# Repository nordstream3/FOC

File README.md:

# King of FOC motor control hardware aka FOC_KING

## The DIY Open Source Vesc6 and FOC capable HW with onboard IMU and CAN
<div>

</div>

Date | Manufacturer | amount | includes | shipping & tax | price
| -------- | -------- | -------- | -------- | -------- | -------- |
2024-01-17 | JLCPCB | 10 boards | All assembled excl fets and caps | YES, to EU | $241.08

An open-source motor controller board based on a JLCPCB friendly [VESC6 75V/300A](https://vesc-project.com/sites/default/files/Benjamin%20Posts/vesc_75_300.pdf) so-called "driverless" design with individual gate drivers for all three phases. It is powered by an STM32F405 MCU and is capable of running FOC at high power and voltages.

A motor controller designed for FOC (Field Oriented Control) and HFI (High Frequency Injection), a sensorless teqnique enabling full torque at zero speed without sensor feedback. The hardware is separated in 3 sub-modules which are assembled using standard pin headers.

POWER BRIDGE | MCU | SUPPLY
|----|----|----|
 |  | 
3 phase power bridge | STM32F405 PILL | +12,+5V,+3V

Intended for "small" electric vehicles like Skateboards, OneWheels, Bicycles, Robotics, Boats, and is designed in sub-modules as a reference design for further development.

The standard design includes 12 mosfets, but it will also work with just 6 fets. You choose.

## Features
* 84V/200A continuous rating
* 20s battery voltage rating
* 3-phase FOC motor control
* 4-layer pcb design with individual gate drivers for all three phases
* STM32F405 MCU
* USB-C
* CAN, 5 mbps
* Onboard IMU (Bosch BMI270)
* Momentary on/off switch connection via 4-pin jst connector
* Led data pin for programmable LEDs
* Compact design with fets mounted on the bottom side
* 12V for gate drivers, 5V for CAN and IMU, and 3.3V for MCU and op-amped current-sense amplification
* Cheap and up-to-date with cheapest and **well stocked** components available for ordering at [JLCPCB](https://jlcpcb.com/) and [LCSC](https://www.lcsc.com)
* **Dimensions of assembled board: 65 x 78 mm**

<div>

</div>

<div>

</div>

[FOC_KING thread on esk8](https://forum.esk8.news/t/f-of-c-open-source-free-of-charge-vesc6-board-in-development-schematics-available/74888/277)

Advantages of separation into modules?
* Suitable for further development by DIY people
* Compatibility with other FOC projects
* Understanding of FOC HW is easier
* HW development is cheaper
* Debugging is easier

Disadvantages
* Assembly takes longer time. You need to solder 46 pinheader pins manually

## How to order at JLCPCB.COM

In the /production folder there is a guide for the [ordering procedure](./production/ordering_guide.md).

## How to assemble

Below is an image of the whole kit needed for assemble. The guide for the [assembly procedure](./production/README.md) is in the /production folder.

## Usage
Use the [VESC Tool](https://vesc-project.com/vesc_tool) to configure the motor controller according to your specific motor and application requirements.

## Contributions
Contributions to this project are welcome and encouraged. If you have any suggestions or improvements, please open an issue or a pull request on the GitHub repository.

## Donate
If you find this project useful and would like to support bread-and-butter for very time consuming development and maintenance, you can [donate 1$](https://www.paypal.com/donate/?business=R5QUC7RNEPKDC&no_recurring=0&item_name=A+small+but+important+contribution+for+Development+and+Maintenance.+Thank+You+very+much.&currency_code=USD) to the creator via [PayPal](https://www.paypal.com/donate/?business=R5QUC7RNEPKDC&no_recurring=0&item_name=A+small+but+important+contribution+for+Development+and+Maintenance.+Thank+You+very+much.&currency_code=USD).

## License
FOC_KING is released under the CERN Open Hardware License (OHL), developed by the European Organization for Nuclear Research. In short, it is a permissive license that allows anyone to use, modify, and distribute the licensed hardware, as long as they provide attribution to the original creators and distribute their modifications under the same license.

## Acknowledgements
FOC_KING is built on the work of the [VESC project](https://github.com/vedderb/bldc) and the contributions of its developers and contributors. Many thanks to *mxlemming* (aka [David Molony](https://github.com/davidmolony/MESC_FOC_ESC)) and *crinq* on the vesc forum on discord for their careful review and advice. Also this project is inspired by the format and concept of the [MP2](https://github.com/badgineer/MP2-ESC) by *badgineer* and the [Cheap Focer2](https://github.com/shamansystems/Cheap-FOCer-2/blob/Developer-Branch/README.md) by *shaman*.

><sub>[markdownguide.org/basic-syntax](https://www.markdownguide.org/basic-syntax/)</sub>  
><sub>[www.markdownguide.org/hacks/](https://www.markdownguide.org/hacks/)</sub>  
><sub>[support.squarespace.com Markdown-cheat-sheet](https://support.squarespace.com/hc/en-us/articles/206543587-Markdown-cheat-sheet)

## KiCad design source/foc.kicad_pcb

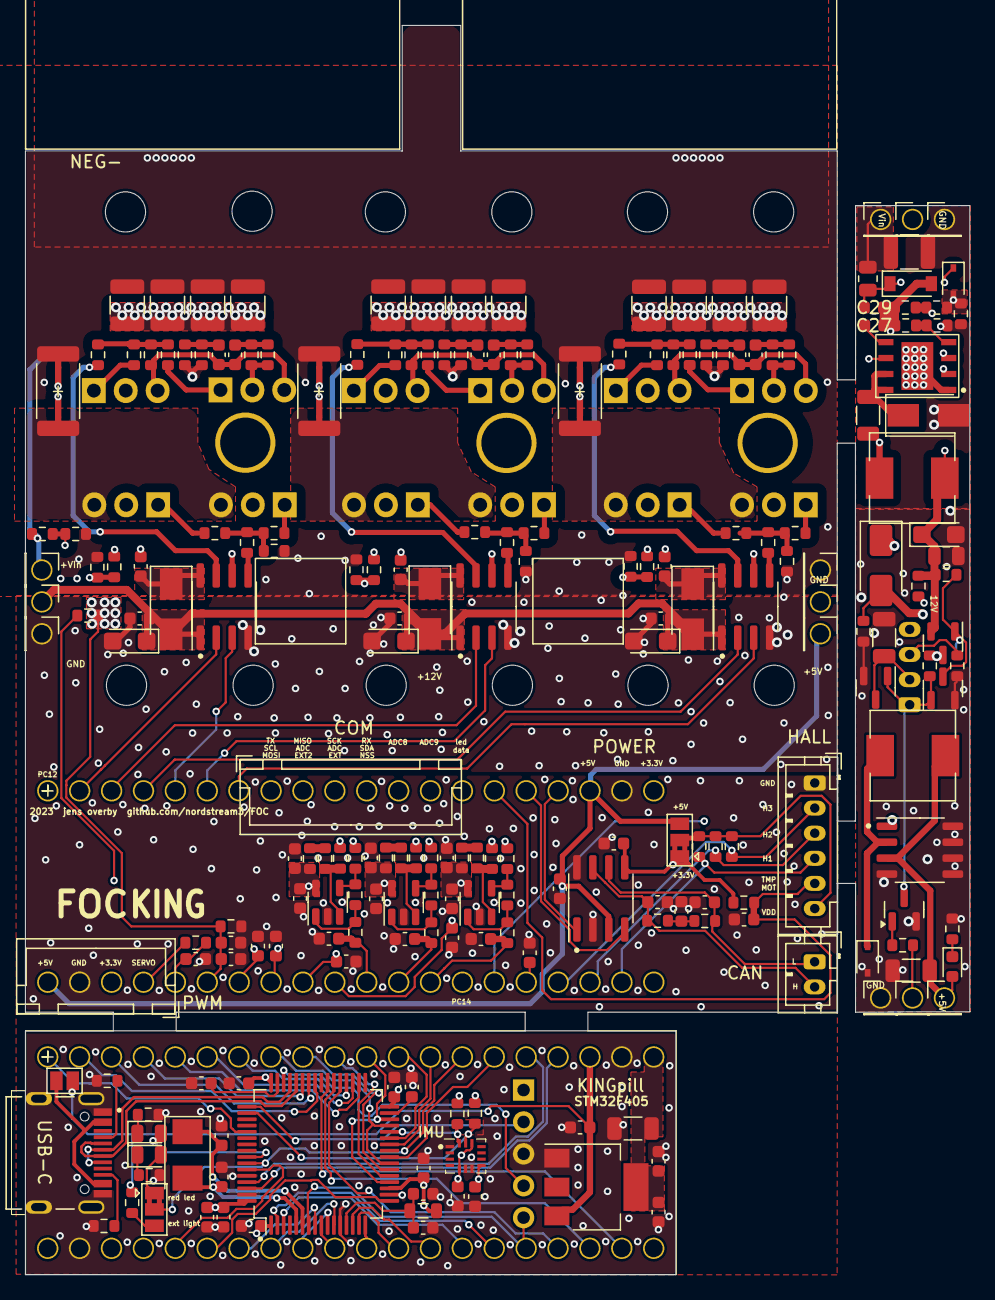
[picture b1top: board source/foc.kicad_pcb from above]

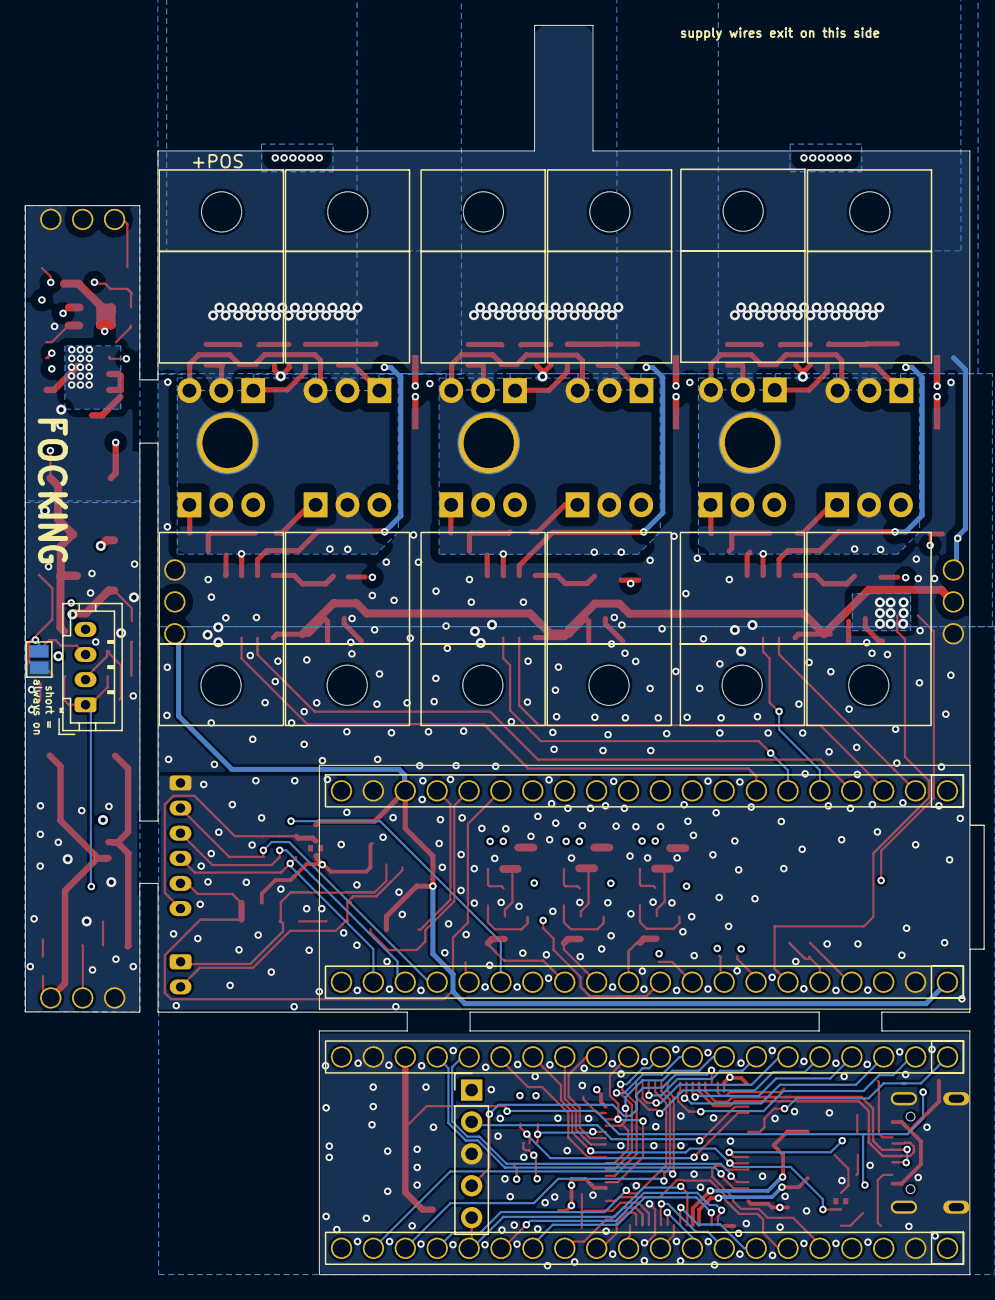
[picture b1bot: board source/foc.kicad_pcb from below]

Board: 4 copper layers, 75.2 x 99.5 mm, 259 parts (20 on the bottom side), 133 nets.

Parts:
C1, C40, C41, C50, C51, C59, C60: 4.7n; C_0603_1608Metric
C2, C3, C12, C18, C22: 100p; C_0603_1608Metric
C4, C7, C11, C15, C16, C19, C25, C27, C29, C33, C42, C45, C52, C64, C65: 2.2u; C_0603_1608Metric
C5, C6, C10, C21, C34, C43, C53, C61, C62, C63, C66, C67, C69, C72, C74: 100n; C_0603_1608Metric
C8, C13, C23: 100u@6.3V; C_1206_3216Metric
C9, C17, C24, C32: 10u; CP_EIA-3216-10_Kemet-I
C14, C20, C28, C75: 10u; C_0603_1608Metric
C26, C36, C37, C38, C39, C46, C47, C48, C49, C55, C56, C57, C58: 4.7u 100V; C_1210_3225Metric
C30, C70: 10n; C_0603_1608Metric
C31: 22u; C_0805_2012Metric
C35, C44, C54: 1n; C_0603_1608Metric
C68: 1u; C_0603_1608Metric
C71, C73: 12p; C_0603_1608Metric
CYA0650-68UH1, CYA0650-68UH2: 68uH; L_6.6x7.2_H5.0_CYA0650_68UH
D1, D2, D4, D7: US1M; D_SMA
D3: 1N5819; D_SOD-323
D5: 1N4148WS; D_SOD-323
D6: MM1W18 1W18V zener; D_SOD-123
D8: SS210; D_SMA
D9: RED; LED_0805_2012Metric
D10: GREEN; LED_0805_2012Metric
D11: WHT; LED_0603_1608Metric
H1, H2, H3, H4, H5, H6, H7, H8, H9, H10, H11, H12: MountingHole; MountingHole_3.2mm_M3
H13: Phase_A_Pad; MountingHole_3.5mm_Pad_TopOnly_custom
H14: Phase_B_Pad; MountingHole_3.5mm_Pad_TopOnly_custom
H15: Phase_C_Pad; MountingHole_3.5mm_Pad_TopOnly_custom
J1: Conn_01x02_Male; JST_PH_B2B-PH-K_1x02_P2.00mm_Vertical
J2: Conn_01x06; JST_PH_B6B-PH-K_1x06_P2.00mm_Vertical
J3: communication; JST_XH_B6B-XH-A_1x06_P2.50mm_Vertical
J4: on/off; JST_PH_B4B-PH-K_1x04_P2.00mm_Vertical
J5: servo; JST_XH_B4B-XH-A_1x04_P2.50mm_Vertical
J6: TYPE-C-31-M-12; HRO_TYPE-C-31-M-12
L1: 10n; L_0805_2012Metric
NT1, NT2, NT3, NT4, NT5, NT6: NetTie_2; NetTie-2_SMD_Pad0.5mm
P1, P2, P3, P4, P5, P6, P7, P8, P9, P10, P12, P13: SWD; PinHeader_1x01_P2.54mm_Vertical
P11: SWD; PinHeader_1x05_P2.54mm_Vertical
Q1: AO3401A; SOT-23
Q2, Q3, Q16: SS8050; SOT-23
Q4, Q5, Q6, Q7, Q8, Q9, Q10, Q11, Q12, Q13, Q14, Q15: CRST030N10N; TO-220-3_Vertical_bend
R1, R2, R3, R11, R15, R17, R19, R28: 2k; R_0603_1608Metric
R4, R5, R85: 100R; R_0603_1608Metric
R6, R13, R26, R86, R87: 5.1k; R_0603_1608Metric
R7, R10, R50, R88, R89: 10k; R_0603_1608Metric
R8, R9: 75k; R_0603_1608Metric
R12: 470k; R_0603_1608Metric
R14, R16, R18, R22, R23, R27, R38, R41, R58, R61, R76, R79: 56k @ 75V; R_0603_1608Metric
R20: 82k @ 150V; R_0805_2012Metric
R21, R24: 1k8; R_0603_1608Metric
R25: 0.1R; R_1206_3216Metric
R29, R47, R67: 150R; R_0603_1608Metric
R30, R49, R68: 30k; R_0603_1608Metric
R31, R32, R43, R44, R45, R46, R51, R52, R63, R64, R65, R66, R69, R70, R81, R82, R83, R84: 10R; R_0603_1608Metric
R33, R92, R93: 56k; R_0603_1608Metric
R34, R35, R54, R55, R72, R73, R96, R97: 1k; R_0603_1608Metric
R36, R37, R39, R40, R56, R57, R59, R60, R74, R75, R77, R78: 4.7R; R_0603_1608Metric
R42, R62, R80: 0.25mR; R_2512_6332Metric
R48: NTC 10k; R_0603_1608Metric
R53, R71, R91: 6.2k; R_0603_1608Metric
R90: 20k; R_0603_1608Metric
SW1, SW4: SW_SPDT; SolderJumper-3_P1.3mm_Bridged2Bar12_Pad1.0x1.5mm
SW2, SW3: SW_SPST; SolderJumper-2_P1.3mm_Open_Pad1.0x1.5mm
U1: TJA1051T/3/1J; SOIC-8_3.9x4.9mm_P1.27mm
U2: BMI270; Bosch_LGA-14_3x2.5mm_P0.5mm
U3: AMS1117-3.3; SOT-223-3_TabPin2
U4, U6, U7: IRS21867S; SOIC-8_3.9x4.9mm_P1.27mm
U5: XL1509-5.0E1; SOP-8_3.9x4.9mm_P1.27mm
U8: TX4130L/PW2902; TX4130L_ESOP-8
U9, U10, U11: MS8311; TSOT-23-5
U12, U13: STM32F401CCU6_Blackpill; Blackpill_STM32F401CEU6
U14: STM32F405RGT6; LQFP-64_10x10mm_P0.5mm
Y1: 8MHz Crystal Resonator, X50328MSB2GI; Crystal_SMD_5032-2Pin_5.0x3.2mm

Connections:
+5V: C4.1, C10.2, C23.1, CYA0650-68UH1.2, D11.2 (A), P4.1, P5.1, R11.1, SW1.3 (C), SW3.1 (A), U1.3 (VCC), U3.3 (VI), U5.3 (FB), U12.20 (5V), U12.38 (5V), U13.20 (5V), U13.38 (5V)
+12V: C9.1, C11.1, C17.1, C19.1, C24.1, C25.1, C31.1, C32.1, CYA0650-68UH2.2, D2.2 (A), D4.2 (A), D5.2 (A), D7.2 (A), P10.1, Q1.2 (S), R8.2, R12.2, R22.1, R26.2, U4.1 (VCC), U6.1 (VCC), U7.1 (VCC)
/driver/H1: U4.2 (HIN), U12.22 (PB13), U13.22 (PB13), U14.41 (PA8)
/driver/H2: U6.2 (HIN), U12.23 (PB14), U13.23 (PB14), U14.42 (PA9(OTG_FS_VBUS))
/driver/H3: U7.2 (HIN), U12.24 (PB15), U13.24 (PB15), U14.43 (PA10)
/driver/HO1: R31.2, U4.7 (HO)
/driver/HO2: R51.2, U6.7 (HO)
/driver/HO3: R69.2, U7.7 (HO)
/driver/HS1: C14.2, C40.1, C41.1, H13.1, Q4.3 (S), Q5.2 (D), Q6.3 (S), Q7.2 (D), R14.2, R38.1, U4.6 (VS)
/driver/HS2: C20.2, C50.1, C51.1, H14.1, Q8.3 (S), Q9.2 (D), Q10.3 (S), Q11.2 (D), R16.2, R58.1, U6.6 (VS)
/driver/HS3: C28.2, C59.1, C60.1, H15.1, Q12.3 (S), Q13.2 (D), Q14.3 (S), Q15.2 (D), R18.2, R76.1, U7.6 (VS)
/driver/L1: U4.3 (LIN), U12.25 (PA8), U13.25 (PA8), U14.34 (PB13(OTG_HS_VBUS))
/driver/L2: U6.3 (LIN), U12.26 (PA9), U13.26 (PA9), U14.35 (PB14)
/driver/L3: U7.3 (LIN), U12.27 (PA10), U13.27 (PA10), U14.36 (PB15)
/driver/LO1: R32.2, U4.5 (LO)
/driver/LO2: R52.2, U6.5 (LO)
/driver/LO3: R70.2, U7.5 (LO)
/driver/MCU_SHUTDOWN: P12.1, P13.1, R6.2, U12.6 (PA0), U13.6 (PA0), U14.2 (PC13_(RTC_AF1))
/driver/SENS_1: C12.2, R14.1, R15.1, U12.13 (PA7), U13.13 (PA7), U14.11 (PC3(ADC123_IN13))
/driver/SENS_2: C18.2, R16.1, R17.1, U12.12 (PA6), U13.12 (PA6), U14.10 (PC2(ADC123_IN12))
/driver/SENS_3: C22.2, R18.1, R19.1, U12.11 (PA5), U13.11 (PA5), U14.9 (PC1(ADC123_IN11))
/driver/SENS_SUPPLY: C30.1, R27.1, R28.1, U12.14 (PB0), U13.14 (PB0), U14.8 (PC0(ADC123_IN10))
/mcu/3.3VA: C68.1, C70.1, L1.2, U14.13 (VDDA)
/mcu/ADC_8: U12.33 (PB5), U13.33 (PB5), U14.26 (PB0(ADC12_IN8))
/mcu/ADC_9: U12.32 (PB4), U13.32 (PB4), U14.27 (PB1(ADC12_IN9))
/mcu/ADC_TEMP: C45.2, C62.1, R48.1, R50.2, U12.15 (PB1), U13.15 (PB1), U14.17 (PA3(ADC123_IN3))
/mcu/CAN_RX: U1.4 (RXD), U12.36 (PB8), U13.36 (PB8), U14.61 (PB8)
/mcu/CAN_TX: U1.1 (TXD), U12.37 (PB9), U13.37 (PB9), U14.62 (PB9)
/mcu/CURRENT_1: C35.1, R29.2, U12.10 (PA4), U13.10 (PA4), U14.16 (PA2(ADC123_IN2))
/mcu/CURRENT_2: C44.1, R47.2, U12.9 (PA3), U13.9 (PA3), U14.15 (PA1(ADC123_IN1))
/mcu/CURRENT_3: C54.1, R67.2, U12.8 (PA2), U13.8 (PA2), U14.14 (PA0(ADC123_IN0/WKUP))
/mcu/HALL_1: J2.4, R1.2, U12.2 (PC13), U13.2 (PC13), U14.39 (PC8)
/mcu/HALL_2: J2.3, R2.2, U12.3 (PC14), U13.3 (PC14), U14.38 (PC7)
/mcu/HALL_3: J2.2, R3.2, U12.4 (PC15), U13.4 (PC15), U14.37 (PC6)
/mcu/LED_GREEN: D10.2 (A), U14.57 (PB5)
/mcu/LED_RED: SW4.2 (B), U12.34 (PB6), U13.34 (PB6), U14.58 (PB6)
/mcu/MISO_ADC_EXT2: U12.29 (PA12), U13.29 (PA12), U14.22 (PA6(ADC12_IN6))
/mcu/NRST: C61.1, P11.5, U12.5 (NRST), U13.5 (NRST), U14.7 (NRST)
/mcu/PA15: R97.1, U2.13 (SCX), U14.50 (PA15(JTDI))
/mcu/PB2: R96.1, U2.14 (SDX), U14.28 (PB2-BOOT1)
/mcu/PC12: U12.21 (PB12), U13.21 (PB12), U14.53 (PC12)
/mcu/PC14: U12.7 (PA1), U13.7 (PA1), U14.3 (PC14-OSC32_IN)
/mcu/PH0: C71.1, U14.6 (PH1-OSC_OUT), Y1.1
/mcu/PH1: C73.1, U14.5 (PH0-OSC_IN), Y1.2
/mcu/RX_SDA_NSS: U12.31 (PB3), U13.31 (PB3), U14.20 (PA4(ADC12_IN4/DAC1_OUT)), U14.30 (PB11)
/mcu/SCK_ADC_EXT: U12.30 (PA15), U13.30 (PA15), U14.21 (PA5(ADC12_IN5/DAC2_OUT))
/mcu/SERVO: C63.1, R85.2, U12.16 (PB2), U13.16 (PB2), U14.59 (PB7)
/mcu/TEMP_MOTOR: C21.1, J2.5, R7.1, U12.35 (PB7), U13.35 (PB7), U14.24 (PC4(ADC12_IN14))
/mcu/TX_SCL_MOSI: U12.28 (PA11), U13.28 (PA11), U14.23 (PA7(ADC12_IN7)), U14.29 (PB10)
/mcu/USB_D+: J6.A6 (DP1), J6.B6 (DP2), U14.45 (PA12)
/mcu/USB_D-: J6.A7 (DN1), J6.B7 (DN2), U14.44 (PA11)
GND: C1.2, C2.2, C3.2, C4.2, C5.1, C6.1, C7.2, C8.2, C9.2, C10.1, C11.2, C12.1, C13.2, C15.1, C16.1, C17.2, C18.1, C19.2, C21.2, C22.1, C23.2, C24.2, C25.2, C26.1, C30.2, C31.2, C32.2, C33.2, C34.2, C35.2, C36.2, C37.2, C38.2, C39.2, C42.2, C43.2, C44.2, C45.1, C46.2, C47.2, C48.2, C49.2, C52.2, C53.2, C54.2, C55.2, C56.2, C57.2, C58.2, C61.2, C62.2, C63.2, C64.2, C65.2, C66.2, C67.2, C68.2, C69.2, C70.2, C71.2, C72.2, C73.2, C74.2, C75.2, D3.2 (A), D8.2 (A), J2.1, J6.A1B12 (GND), J6.B1A12 (GND), J6.S1 (SHIELD), J6.S2 (SHIELD), J6.S3 (SHIELD), J6.S4 (SHIELD), NT2.2, NT4.2, NT6.2, P2.1, P3.1, P8.1, P9.1, P11.3, Q2.2 (E), Q3.2 (E), Q16.2 (E), R10.2, R13.1, R15.2, R17.2, R19.2, R23.1, R26.1, R28.2, R41.1, R42.1, R44.2, R46.2, R50.1, R61.1, R62.1, R64.2, R66.2, R79.1, R80.1, R82.2, R84.2, R86.2, R87.2, R88.1, R89.1, R90.1, SW2.2 (B), U1.2 (GND), U1.8 (S), U2.1 (SDO), U2.6 (GNDIO), U2.7 (GND), U3.1 (GND), U4.4 (COM), U5.4 (O/O), U5.5 (GND), U5.6 (GND), U5.7 (GND), U5.8 (GND), U6.4 (COM), U7.4 (COM), U9.2 (V-), U10.2 (V-), U11.2 (V-), U12.19 (GND), U12.39 (GND), U13.19 (GND), U13.39 (GND), U14.12 (VSSA), U14.18 (VSS), U14.60 (BOOT0(VPP)), U14.63 (VSS)
unnamed: C1.1, R4.1, R5.2
unnamed: C40.2, R43.1, R45.1
unnamed: C41.2, R44.1, R46.1
unnamed: C50.2, R63.1, R65.1
unnamed: C51.2, R64.1, R66.1
unnamed: C59.2, R81.1, R83.1
unnamed: C60.2, R82.1, R84.1
unnamed: D1.2 (A), Q1.3 (D), R9.2, R13.2
unnamed: D1.1 (K), J4.4, P1.1, U5.1 (Vin)
unnamed: C14.1, D2.1 (K), U4.8 (VB)
unnamed: CYA0650-68UH1.1, D3.1 (K), U5.2 (Vout)
unnamed: C20.1, D4.1 (K), U6.8 (VB)
unnamed: C27.2, D5.1 (K), D6.1 (K), R20.1, U8.2 (VDD)
unnamed: C27.1, C29.2, CYA0650-68UH2.1, D6.2 (A), R21.1, R24.1, R25.1, U8.6 (VSS)
unnamed: C28.1, D7.1 (K), U7.8 (VB)
unnamed: D8.1 (K), R25.2, U8.7 (VSEN), U8.8 (VSEND)
unnamed: D9.2 (A), SW4.1 (A)
unnamed: D9.1 (K), R88.2
unnamed: D10.1 (K), R89.2
unnamed: D11.1 (K), R90.2
unnamed: C3.1, J1.1, R5.1, U1.6 (CANL)
unnamed: C2.1, J1.2, R4.2, U1.7 (CANH)
unnamed: J2.6, R1.1, R2.1, R3.1, SW1.2 (B)
unnamed: J4.1, Q2.1 (B), Q3.1 (B), Q16.3 (C), R9.1
unnamed: C8.1, J4.2, Q3.3 (C), R12.1
unnamed: J4.3, R10.1
unnamed: R85.1, U12.17 (PB10)
unnamed: J6.A5 (CC1), R86.1
unnamed: J6.B5 (CC2), R87.1
unnamed: NT1.1, R34.1
unnamed: NT2.1, R35.1
unnamed: NT3.1, R54.1
unnamed: NT4.1, R55.1
unnamed: NT5.1, R72.1
unnamed: NT6.1, R73.1
unnamed: P11.2, U14.49 (PA14(JTCK-SWCLK))
unnamed: P11.4, U14.46 (PA13(JTMS-SWDIO))
unnamed: Q1.1 (G), Q2.3 (C), R8.1, SW2.1 (A)
unnamed: Q4.1 (G), R36.1
unnamed: Q5.1 (G), R39.1
unnamed: NT1.2, Q5.3 (S), Q7.3 (S), R42.2
unnamed: Q6.1 (G), R37.1
unnamed: Q7.1 (G), R40.1
unnamed: Q8.1 (G), R56.1
unnamed: Q9.1 (G), R59.1
unnamed: Q10.1 (G), R57.1
unnamed: Q11.1 (G), R60.1
unnamed: NT3.2, Q9.3 (S), Q11.3 (S), R62.2
unnamed: Q12.1 (G), R74.1
unnamed: Q13.1 (G), R77.1
unnamed: NT5.2, Q13.3 (S), Q15.3 (S), R80.2
unnamed: Q14.1 (G), R75.1
unnamed: Q15.1 (G), R78.1
unnamed: Q16.1 (B), R6.1
unnamed: R29.1, R30.2, U9.1
unnamed: R31.1, R36.2, R37.2, R38.2
unnamed: R32.1, R39.2, R40.2, R41.2
unnamed: R33.2, R91.1
unnamed: R47.1, R49.2, U10.1
unnamed: R51.1, R56.2, R57.2, R58.2
unnamed: R52.1, R59.2, R60.2, R61.2
unnamed: R53.1, R92.2
unnamed: R67.1, R68.2, U11.1
unnamed: R69.1, R74.2, R75.2, R76.2
unnamed: R70.1, R77.2, R78.2, R79.2
unnamed: R71.1, R93.2
unnamed: J6.A4B9 (VBUS), J6.B4A9 (VBUS), SW3.2 (B)
unnamed: R11.2, SW4.3 (C)
unnamed: R21.2, R22.2, U8.3 (FB1)
unnamed: R23.2, R24.2, U8.4 (FB2)
unnamed: C29.1, U8.5 (LDO)
unnamed: R33.1, R35.2, U9.3 (+)
unnamed: R30.1, R34.2, U9.4 (-)
unnamed: R55.2, R92.1, U10.3 (+)
unnamed: R49.1, R54.2, U10.4 (-)
unnamed: R73.2, R93.1, U11.3 (+)
unnamed: R68.1, R72.2, U11.4 (-)
unnamed: C65.1, U14.31 (VCAP1)
unnamed: C64.1, U14.47 (VCAP2)
VCC: C5.2, C6.2, C7.1, C13.1, C15.2, C16.2, C33.1, C34.1, C42.1, C43.1, C52.1, C53.1, C66.1, C67.1, C69.1, C72.1, C74.1, C75.1, L1.1, P11.1, R7.2, R48.2, R53.2, R71.2, R91.2, R96.2, R97.2, SW1.1 (A), U1.5 (VIO), U2.5 (VDDIO), U2.8 (VDD), U2.12 (CSB), U3.2 (VO), U9.5 (V+), U10.5 (V+), U11.5 (V+), U12.18 (3V3), U12.40 (3V3), U13.18 (3V3), U13.40 (3V3), U14.1 (VBAT), U14.19 (VDD), U14.32 (VDD), U14.48 (VDD), U14.64 (VDD)
V_IN: C26.2, C36.1, C37.1, C38.1, C39.1, C46.1, C47.1, C48.1, C49.1, C55.1, C56.1, C57.1, C58.1, P6.1, P7.1, Q4.2 (D), Q6.2 (D), Q8.2 (D), Q10.2 (D), Q12.2 (D), Q14.2 (D), R20.2, R27.2, R43.2, R45.2, R63.2, R65.2, R81.2, R83.2, U8.1 (VIN), U8.9 (VIN)

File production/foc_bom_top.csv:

"Comment","Designator","Footprint","LCSC Part #"
"4.7n","C1","","C53987"
"100p","C2 C3 C12 C18 C22","","C14858"
"2.2u","C4 C7 C11 C15 C16 C19 C25 C27 C29 C33 C42 C45 C52 C64 C65","","C23630"
"100n","C5 C6 C21 C10 C34 C43 C53 C61 C62 C63 C66 C67 C69 C72 C74","","C14663"
"Conn_01x02_Male","J1","",""
"Conn_01x06","J2","",""
"communication","J3","",""
"2k","R1 R2 R3 R15 R17 R19 R28 R11","","C22975"
"100R","R4 R5 R85","","C22775"
"10k","R7 R10 R50 R88 R89","","C25804"
"1k","R96 R97 R34 R35 R54 R55 R72 R73","","C21190"
"SW_SPDT","SW1 SW4","",""
"TJA1051T/3/1J","U1","","C38695"
"BMI270","U2","","C2836813"
"100u@6.3V","C8 C13 C23","","C15008"
"10u","C9 C17 C24 C32","","C7171"
"10u","C14 C20 C28 C75","","C96446"
"4.7u 100V","C26 C36 C37 C38 C39 C46 C47 C48 C49 C55 C56 C57 C58","","C381466"
"10n","C30 C70","","C57112"
"22u","C31","","C45783"
"68uH","CYA0650-68UH1 CYA0650-68UH2","","C5189964"
"US1M","D1 D2 D4 D7","","C412437"
"1N5819","D3","","C191023"
"1N4148WS","D5","","C2128"
"MM1W18 1W18V zener","D6","","C382948"
"SS210","D8","","C14996"
"SWD","P1 P2 P3 P4 P5 P6 P7 P8 P9 P10 P12 P13","",""
"AO3401A","Q1","","C15127"
"SS8050","Q2 Q3 Q16","","C2150"
"5.1k","R6 R13 R26 R86 R87","","C23186"
"75k","R8 R9","","C23242"
"470k","R12","","C23178"
"56k @ 75V","R14 R16 R18 R22 R23 R27 R38 R41 R58 R61 R76 R79","","C23206"
"82k @ 150V","R20","","C17840"
"1k8","R21 R24","","C4177"
"0.1R","R25","","C25334"
"AMS1117-3.3","U3","","C6186"
"IRS21867S","U4 U6 U7","","C52290"
"XL1509-5.0E1","U5","","C61063"
"TX4130L/PW2902","U8","","C448635"
"1n","C35 C44 C54","","C1588"
"4.7n","C40 C41 C50 C51 C59 C60","","C382251"
"150R","R29 R47 R67","","C22808"
"30k","R30 R49 R68","","C22984"
"10R","R31 R32 R43 R44 R45 R46 R51 R52 R63 R64 R65 R66 R69 R70 R81 R82 R83 R84","","C22859"
"56k","R33 R92 R93","","C23206"
"4.7R","R36 R37 R39 R40 R56 R57 R59 R60 R74 R75 R77 R78","","C23164"
"0.25mR","R42 R62 R80","","C495759"
"NTC 10k","R48","","C13564"
"6.2k","R53 R71 R91","","C4260"
"MS8311","U9","","C1509000"
"MS8311","U10 U11","",""
"1u","C68","","C15849"
"12p","C71 C73","","C38523"
"RED","D9","","C84256"
"GREEN","D10","","C2297"
"WHT","D11","","C2290"
"servo","J5","",""
"TYPE-C-31-M-12","J6","","C165948"
"10n","L1",""," C1046"
"20k","R90","","C4184"
"SW_SPST","SW3","",""
"STM32F405RGT6","U14","","C15742"
"8MHz Crystal Resonator, X50328MSB2GI","Y1","","C115962"

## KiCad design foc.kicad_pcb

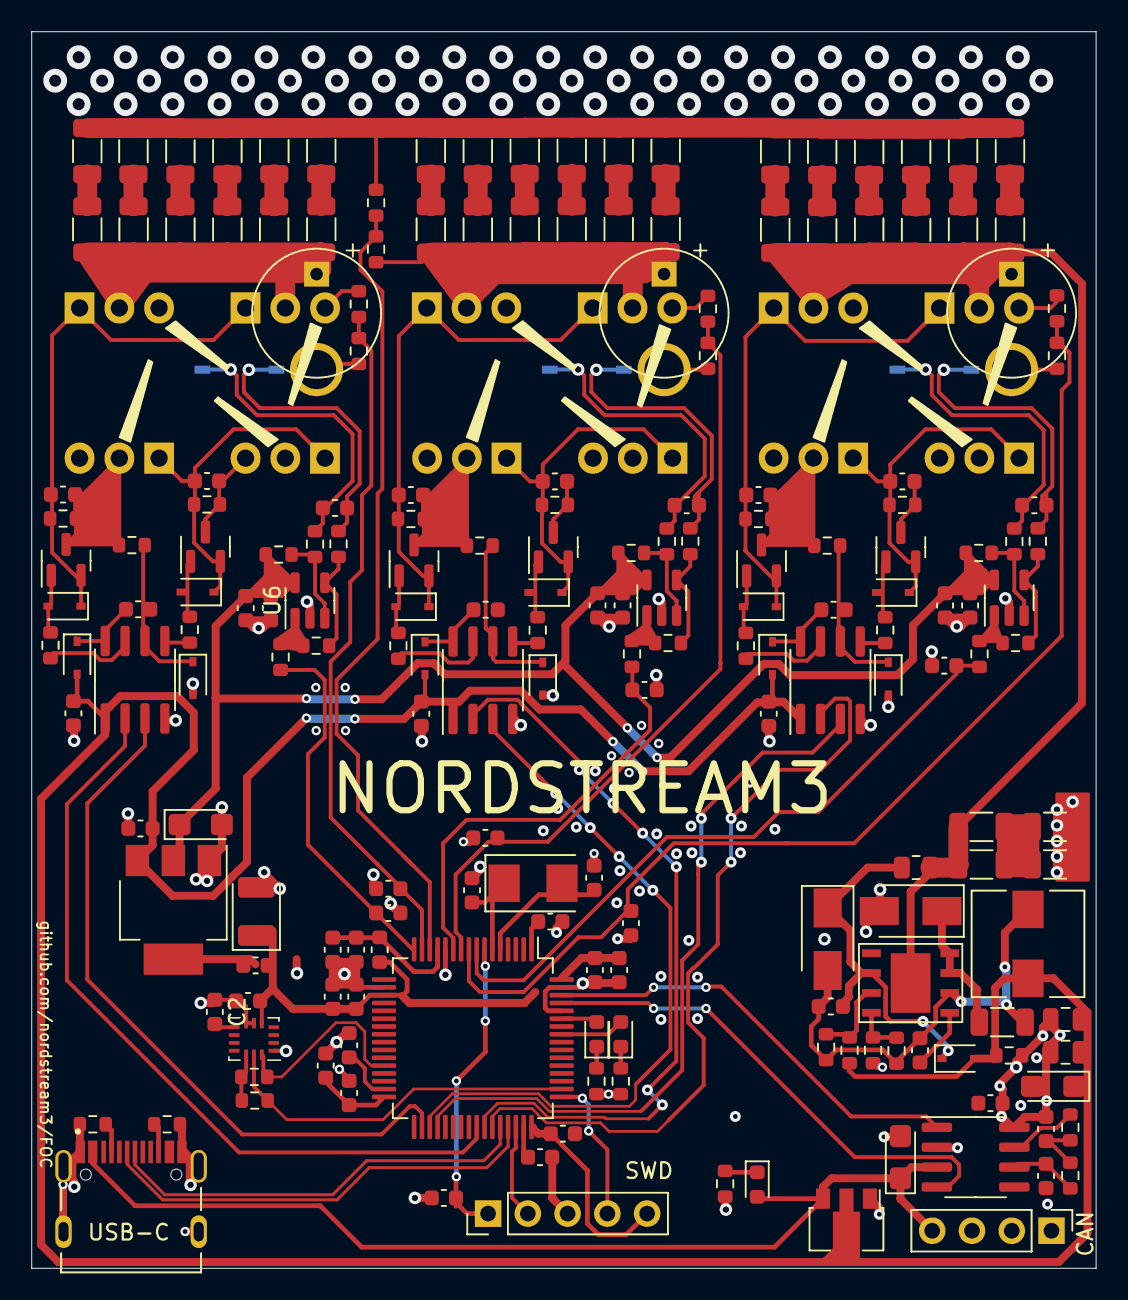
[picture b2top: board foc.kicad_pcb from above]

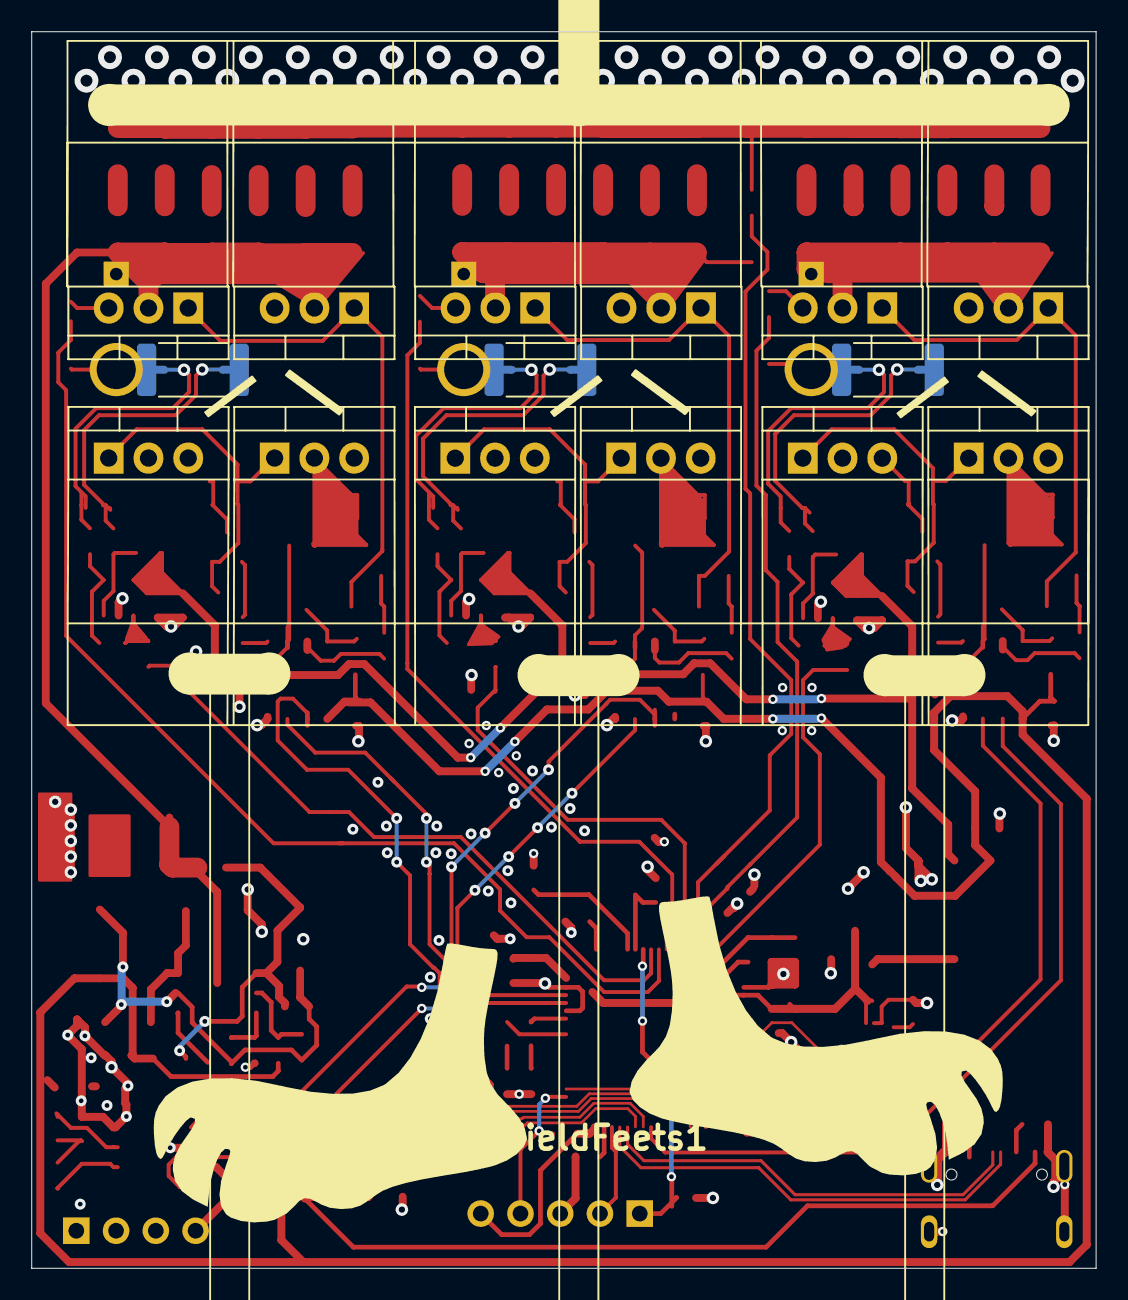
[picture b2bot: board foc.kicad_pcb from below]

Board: 2 copper layers, 68.0 x 79.0 mm, 218 parts (22 on the bottom side), 113 nets.

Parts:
C1, C2, C5, C8, C19, C25, C44, C63, C83, C84, C85, C93, C94, C97, C101, C103: 100n; C_0603_1608Metric
C3, C4, C7, C17, C18, C20, C24, C43, C64, C89, C90, C91, C92, C104, C105, C106: 2.2u; C_0603_1608Metric
C6: 100u; CP_EIA-3528-21_Kemet-B
C9, C10, C11, C12, C30, C31, C32, C33, C34, C35, C36, C37, C38, C39, C40, C41, C50, C51, C52, C53, C54, C55, C56, C57, C58, C59, C60, C61, C69, C70, C71, C72, C73, C74, C75, C76, C77, C78, C79, C80: 10u @ 50V; C_1206_3216Metric
C21, C22: 22u; C_0805_2012Metric
C23, C88, C107: 10u; CP_EIA-3216-10_Kemet-I
C26, C45, C65: 1n; C_0603_1608Metric
C27, C28, C47, C48, C66, C67: 2.2nF; C_0603_1608Metric
C29, C49, C68, C86, C87: 100p; C_0603_1608Metric
C42, C62, C81: 470u 80V; CP_Radial_D8.0mm_P5.00mm
C82: 4.7n; C_0603_1608Metric
C96: 1u; C_0603_1608Metric
C98: 10n; C_0603_1608Metric
C99, C102: 15p; C_0603_1608Metric
CYA0650-68UH1: 68uH; L_6.6x7.2_H5.0_CYA0650_68UH
D1, D2, D3, D4, D5, D7, D8, D10, D11, D12, D13, D14, D15: 1N4148WS; D_SOD-323
D6, D9: SS210; D_SMA
D16: RED; LED_0603_1608Metric
D17: GRN; LED_0603_1608Metric
D18: BLU; LED_0603_1608Metric
FieldFeets1: R; field
J1: Conn_01x04_Male; PinHeader_1x04_P2.54mm_Vertical
J2: TYPE-C-31-M-12; HRO_TYPE-C-31-M-12
L1: 30n; L_0603_1608Metric
NT1, NT2, NT3, NT4, NT5, NT6: NetTie_2; NetTie-2_SMD_Pad0.5mm
P1: SWD; PinHeader_1x05_P2.54mm_Vertical
Q1, Q2, Q7, Q8, Q13, Q14: MMBT5401; SOT-23
Q3: NCEP60T20; TO-220-3_Vertical
Q4, Q5, Q6, Q9, Q10, Q11, Q12, Q15, Q16, Q17, Q18: CSD19536KCS; TO-220-3_Vertical
R1, R2, R28, R29, R40, R41, R50, R51: 1k; R_0603_1608Metric
R3, R6, R8, R12: 56k @ 75V; R_0603_1608Metric
R4, R7, R9, R13, R20: 2k; R_0603_1608Metric
R5, R10, R15: 2R; R_0603_1608Metric
R11: 82k @ 150V; R_0805_2012Metric
R14, R18: 1k8; R_0603_1608Metric
R16, R17: 56k; R_0603_1608Metric
R19: 0.1R; R_1206_3216Metric
R21, R24, R31, R35, R43, R46: 30k; R_0603_1608Metric
R22, R23, R33, R34, R44, R45: 4.7R; R_0603_1608Metric
R25, R37, R47: 62k; R_0603_1608Metric
R26, R27, R38, R39, R48, R49: 4.7k @ 75v; R_0603_1608Metric
R30, R42, R52: ASR-M-3-0.25F 0.25mR; R_2512_6332Metric
R53, R54: 100Ω; R_0603_1608Metric
R55, R56: 5.1k; R_0603_1608Metric
R57, R58, R59: 20k; R_0603_1608Metric
U1: BMI160; Bosch_LGA-14_3x2.5mm_P0.5mm
U2, U3, U4: IRS21867S; SOIC-8_3.9x4.9mm_P1.27mm
U5: TX4130L/PW2902; TX4130L_ESOP-8
U6, U7, U8: MS8311; TSOT-23-5
U9: TJA1050T/CM,118; SOIC-8_3.9x4.9mm_P1.27mm
U10: HT7550; SOT-89-3
U11: STM32F405RGT6; LQFP-64_10x10mm_P0.5mm
U12: AMS1117-3.3; SOT-223-3_TabPin2
Y1: 8MHz Crystal Resonator, X50328MSB2GI; Crystal_SMD_5032-2Pin_5.0x3.2mm

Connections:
+5V: C88.1, D18.2 (A), J1.4, J2.A4B9 (VBUS), J2.B4A9 (VBUS), U9.3 (VCC), U10.3 (VO)
+12V: C3.1, C7.1, C17.1, C21.1, C22.1, C23.1, C103.2, CYA0650-68UH1.2, D1.2 (A), D3.2 (A), D5.2 (A), D7.2 (A), R16.1, R20.2, U2.1 (VCC), U3.1 (VCC), U4.1 (VCC), U10.2 (VI), U12.3 (VI)
/driver/H1: U2.2 (HIN), U11.41 (PA8)
/driver/H2: U3.2 (HIN), U11.42 (PA9(OTG_FS_VBUS))
/driver/H3: U4.2 (HIN), U11.43 (PA10)
/driver/HO1: R22.1, U2.7 (HO)
/driver/HO2: R33.1, U3.7 (HO)
/driver/HO3: R44.1, U4.7 (HO)
/driver/HS1: C27.2, Q1.3 (C), Q3.3 (S), Q4.2 (D), Q5.3 (S), Q6.2 (D), R3.2, R5.2, R26.1
/driver/HS2: C47.2, Q7.3 (C), Q9.3 (S), Q10.2 (D), Q11.3 (S), Q12.2 (D), R8.2, R10.2, R38.1
/driver/HS3: C66.2, Q13.3 (C), Q15.3 (S), Q16.2 (D), Q17.3 (S), Q18.2 (D), R12.2, R15.2, R48.1
/driver/L1: U2.3 (LIN), U11.34 (PB13(OTG_HS_VBUS))
/driver/L2: U3.3 (LIN), U11.35 (PB14)
/driver/L3: U4.3 (LIN), U11.36 (PB15)
/driver/LO1: R23.1, U2.5 (LO)
/driver/LO2: R34.1, U3.5 (LO)
/driver/LO3: R45.1, U4.5 (LO)
/driver/SENS_1: C83.1, R3.1, R4.1, U11.15 (PA1(ADC123_IN1))
/driver/SENS_2: C84.1, R8.1, R9.1, U11.10 (PC2(ADC123_IN12))
/driver/SENS_3: C85.1, R12.1, R13.1, U11.9 (PC1(ADC123_IN11))
/driver/SENS_SUPPLY: R6.1, R7.1, U11.14 (PA0(ADC123_IN0/WKUP))
/mcu/3.3VA: C96.1, C98.1, L1.2, U11.13 (VDDA)
/mcu/CAN_RX: U9.4 (RXD), U11.61 (PB8)
/mcu/CAN_TX: U9.1 (TXD), U11.62 (PB9)
/mcu/CURRENT_1: C26.2, R21.2, U11.16 (PA2(ADC123_IN2))
/mcu/CURRENT_2: C45.2, R31.2, U11.11 (PC3(ADC123_IN13))
/mcu/CURRENT_3: C65.2, R43.2, U11.8 (PC0(ADC123_IN10))
/mcu/LED_GREEN: D17.2 (A), U11.57 (PB5)
/mcu/LED_RED: D16.2 (A), U11.59 (PB7)
/mcu/NRST: C93.2, P1.1, U11.7 (NRST)
/mcu/PA15: R2.2, U1.13 (SCX), U11.50 (PA15(JTDI))
/mcu/PB2: R1.1, U1.14 (SDX), U11.28 (PB2-BOOT1)
/mcu/PH0: C99.1, U11.6 (PH1-OSC_OUT), Y1.1
/mcu/PH1: C102.1, U11.5 (PH0-OSC_IN), Y1.2
/mcu/SWCLK: P1.4, U11.49 (PA14(JTCK-SWCLK))
/mcu/SWDIO: P1.2, U11.46 (PA13(JTMS-SWDIO))
/mcu/USB_D+: J2.A6 (DP1), J2.B6 (DP2), U11.45 (PA12)
/mcu/USB_D-: J2.A7 (DN1), J2.B7 (DN2), U11.44 (PA11)
GND: C1.1, C2.1, C3.2, C4.2, C6.2, C7.2, C10.1, C12.2, C17.2, C21.2, C22.2, C23.2, C24.1, C25.1, C26.1, C31.1, C33.1, C35.1, C37.1, C39.1, C41.1, C42.2, C43.1, C44.1, C45.1, C51.1, C53.1, C55.1, C57.1, C59.1, C61.1, C62.2, C63.2, C64.2, C65.1, C70.1, C72.1, C74.1, C76.1, C78.1, C80.1, C81.2, C82.2, C83.2, C84.2, C85.2, C86.2, C87.2, C88.2, C89.2, C90.2, C91.2, C92.2, C93.1, C94.2, C96.2, C97.2, C98.2, C99.2, C101.2, C102.2, C103.1, C104.1, C105.1, C106.1, C107.2, D2.2 (A), D4.2 (A), D8.2 (A), D9.2 (A), J1.1, J2.A1B12 (GND), J2.B1A12 (GND), J2.S1 (SHIELD), J2.S2 (SHIELD), J2.S3 (SHIELD), J2.S4 (SHIELD), NT2.2, NT4.2, NT6.2, P1.3, R4.2, R7.2, R9.2, R13.2, R17.1, R20.1, R30.2, R42.2, R52.2, R55.2, R56.2, R57.1, R58.1, R59.1, U1.1 (SDO), U1.6 (GNDIO), U1.7 (GND), U2.4 (COM), U3.4 (COM), U4.4 (COM), U6.2 (V-), U7.2 (V-), U8.2 (V-), U9.2 (GND), U9.8 (S), U10.1 (GND), U11.12 (VSSA), U11.18 (VSS), U11.60 (BOOT0(VPP)), U11.63 (VSS), U12.1 (GND)
unnamed: C5.1, D1.1 (K), U2.8 (VB)
unnamed: C5.2, D2.1 (K), R5.1, U2.6 (VS)
unnamed: C8.1, D3.1 (K), U3.8 (VB)
unnamed: C8.2, D4.1 (K), R10.1, U3.6 (VS)
unnamed: C9.1, C10.2
unnamed: C11.2, C12.1
unnamed: C18.1, C20.1, CYA0650-68UH1.1, D6.2 (A), R14.1, R18.1, R19.1, U5.6 (VSS)
unnamed: C18.2, D5.1 (K), D6.1 (K), R11.1, U5.2 (VDD)
unnamed: C19.1, D7.1 (K), U4.8 (VB)
unnamed: C19.2, D8.1 (K), R15.1, U4.6 (VS)
unnamed: C20.2, U5.5 (LDO)
unnamed: C27.1, D10.1 (K), Q1.2 (E), Q3.1 (G), Q5.1 (G), R26.2
unnamed: C28.1, D11.1 (K), Q2.2 (E), Q4.1 (G), Q6.1 (G), R27.2
unnamed: C28.2, NT1.2, Q2.3 (C), Q4.3 (S), Q6.3 (S), R27.1, R30.1
unnamed: C29.1, NT2.1, R29.1
unnamed: C29.2, NT1.1, R28.1
unnamed: C30.1, C31.2
unnamed: C32.1, C33.2
unnamed: C34.1, C35.2
unnamed: C36.1, C37.2
unnamed: C38.1, C39.2
unnamed: C40.1, C41.2
unnamed: C47.1, D12.1 (K), Q7.2 (E), Q9.1 (G), Q11.1 (G), R38.2
unnamed: C48.1, D13.1 (K), Q8.2 (E), Q10.1 (G), Q12.1 (G), R39.2
unnamed: C48.2, NT3.2, Q8.3 (C), Q10.3 (S), Q12.3 (S), R39.1, R42.1
unnamed: C49.1, NT4.1, R41.1
unnamed: C49.2, NT3.1, R40.1
unnamed: C50.1, C51.2
unnamed: C52.1, C53.2
unnamed: C54.1, C55.2
unnamed: C56.1, C57.2
unnamed: C58.1, C59.2
unnamed: C60.1, C61.2
unnamed: C66.1, D14.1 (K), Q13.2 (E), Q15.1 (G), Q17.1 (G), R48.2
unnamed: C67.1, D15.1 (K), Q14.2 (E), Q16.1 (G), Q18.1 (G), R49.2
unnamed: C67.2, NT5.2, Q14.3 (C), Q16.3 (S), Q18.3 (S), R49.1, R52.1
unnamed: C68.1, NT6.1, R51.1
unnamed: C68.2, NT5.1, R50.1
unnamed: C69.1, C70.2
unnamed: C71.1, C72.2
unnamed: C73.1, C74.2
unnamed: C75.1, C76.2
unnamed: C77.1, C78.2
unnamed: C79.1, C80.2
unnamed: C82.1, R53.1, R54.2
unnamed: C86.1, J1.3, R53.2, U9.7 (CANH)
unnamed: C87.1, J1.2, R54.1, U9.6 (CANL)
unnamed: C89.1, U11.47 (VCAP2)
unnamed: C90.1, U11.31 (VCAP1)
unnamed: D9.1 (K), R19.2, U5.7 (VSEN), U5.8 (VSEND)
unnamed: D10.2 (A), Q1.1 (B), R22.2
unnamed: D11.2 (A), Q2.1 (B), R23.2
unnamed: D12.2 (A), Q7.1 (B), R33.2
unnamed: D13.2 (A), Q8.1 (B), R34.2
unnamed: D14.2 (A), Q13.1 (B), R44.2
unnamed: D15.2 (A), Q14.1 (B), R45.2
unnamed: D16.1 (K), R57.2
unnamed: D17.1 (K), R58.2
unnamed: D18.1 (K), R59.2
unnamed: J2.A5 (CC1), R55.1
unnamed: J2.B5 (CC2), R56.1
unnamed: R14.2, R16.2, U5.3 (FB1)
unnamed: R17.2, R18.2, U5.4 (FB2)
unnamed: R21.1, R24.2, U6.1
unnamed: R24.1, R29.2, U6.4 (-)
unnamed: R25.1, R28.2, U6.3 (+)
unnamed: R31.1, R35.2, U7.1
unnamed: R35.1, R41.2, U7.4 (-)
unnamed: R37.1, R40.2, U7.3 (+)
unnamed: R43.1, R46.2, U8.1
unnamed: R46.1, R51.2, U8.4 (-)
unnamed: R47.1, R50.2, U8.3 (+)
VCC: C1.2, C2.2, C4.1, C6.1, C24.2, C25.2, C43.2, C44.2, C63.1, C64.1, C91.1, C92.1, C94.1, C97.1, C101.1, C104.2, C105.2, C106.2, C107.1, L1.1, P1.5, R1.2, R2.1, R25.2, R37.2, R47.2, U1.5 (VDDIO), U1.8 (VDD), U1.12 (CSB), U6.5 (V+), U7.5 (V+), U8.5 (V+), U11.1 (VBAT), U11.19 (VDD), U11.32 (VDD), U11.48 (VDD), U11.64 (VDD), U12.2 (VO)
V_IN: C9.2, C11.1, C30.2, C32.2, C34.2, C36.2, C38.2, C40.2, C42.1, C50.2, C52.2, C54.2, C56.2, C58.2, C60.2, C62.1, C69.2, C71.2, C73.2, C75.2, C77.2, C79.2, C81.1, Q3.2 (D), Q5.2 (D), Q9.2 (D), Q11.2 (D), Q15.2 (D), Q17.2 (D), R6.2, R11.2, U5.1 (VIN), U5.9 (VIN)

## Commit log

2023-06-07 4 layer design
2023-08-24 First 4 layer order at JLCPCB
2023-10-06 Add files via upload
    Filter resistor on current op-amps changed from 30k to 150R
    Mosfets at 45 deg angle
    Changed layout of power supply
    Cut through center of board
    Unnecessary components near mosfets removed
    Voltage filters removed again
2023-10-17 2 board setup with mcu and foc shield separated
2023-10-30 Add files via upload
    2 missing gnd connections on mcu
    missing gnd connection on 12V power supply
    pin4 pulled to gnd on 5V power supply
2023-11-05 JLCPCB order with separate power supply
2023-11-05 JLCPCB order with separate power supplty
2023-11-08 jlcpcb order
2023-11-12 Add files via upload
    Bugs in the jlcbpcb order, so it was cancelled. This commit marks a new jlcpcb order.
2023-11-28 jlcpcb reorder of main-module only
2023-11-28 jlcpcb reorder of main module only
2023-12-17 Add files via upload
    Added six pull down resistors to mosfet gates, and removed 100 pF filter caps on current samplings. Changed Logo back to FOC-king. This is a potential release candidates - everything works, also HFI.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
2024-01-03 Moved traces to make peripherals work
    PPM now works -> moved trace to PB7
    UART works -> connected PB10 and PB11 to Communication port (like vesc 75_300 UART)
    Removed NRF24 pinheader
    Added motor_temperature to Hall pinheader, like it should be
2024-01-03 Create ddd
2024-01-03 Pcb order as of 01.03.24
2024-01-07 moved images to folder
2024-01-12 CAN without 5V
2024-01-22 Documentation
2024-02-02 Add files via upload
    LCSC number for 330uF is now correct
2024-03-20 Momentary switch
2024-03-22 Yellow LED resistor from 10k to 5k
2024-04-08 V1.0
2025-03-11 New bosch IMU, automatic shutdown, momentary sw.
2025-03-11 Create vesc_source_code
2025-04-24 Rename project
2025-04-24 changed flag p1 to p2
2025-04-24 DRC run
2025-04-24 Using jlcpcb fabrication plugin
